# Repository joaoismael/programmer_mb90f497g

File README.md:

# programmer_mb90f497g
Programmer for MB90f497G - Aprilia RSV1000R Factory Dashboard

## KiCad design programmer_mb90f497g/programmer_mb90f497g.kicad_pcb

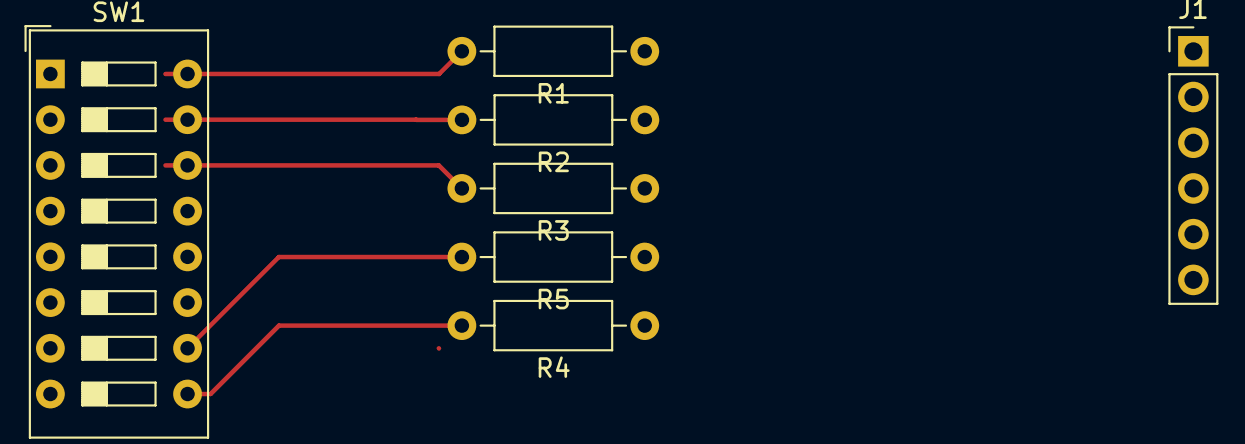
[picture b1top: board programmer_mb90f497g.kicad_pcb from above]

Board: 2 copper layers, 7 parts (0 on the bottom side), 7 nets.

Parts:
J1: Conn_01x06_Pin; PinHeader_1x06_P2.54mm_Vertical
R1, R2, R3, R4, R5: 10K; R_Axial_DIN0207_L6.3mm_D2.5mm_P10.16mm_Horizontal
SW1: SW_DIP_x08; SW_DIP_SPSTx08_Slide_9.78x22.5mm_W7.62mm_P2.54mm

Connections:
GND: J1.1, SW1.1, SW1.2, SW1.3, SW1.7, SW1.8
MD0: R1.2, SW1.16
MD1: R2.2, SW1.15
MD2: R3.2, SW1.14
P00: R4.2, SW1.9
P01: R5.2, SW1.10
VCC: J1.3, R1.1, R2.1, R3.1, R4.1, R5.1

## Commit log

2024-02-13 Upload project
